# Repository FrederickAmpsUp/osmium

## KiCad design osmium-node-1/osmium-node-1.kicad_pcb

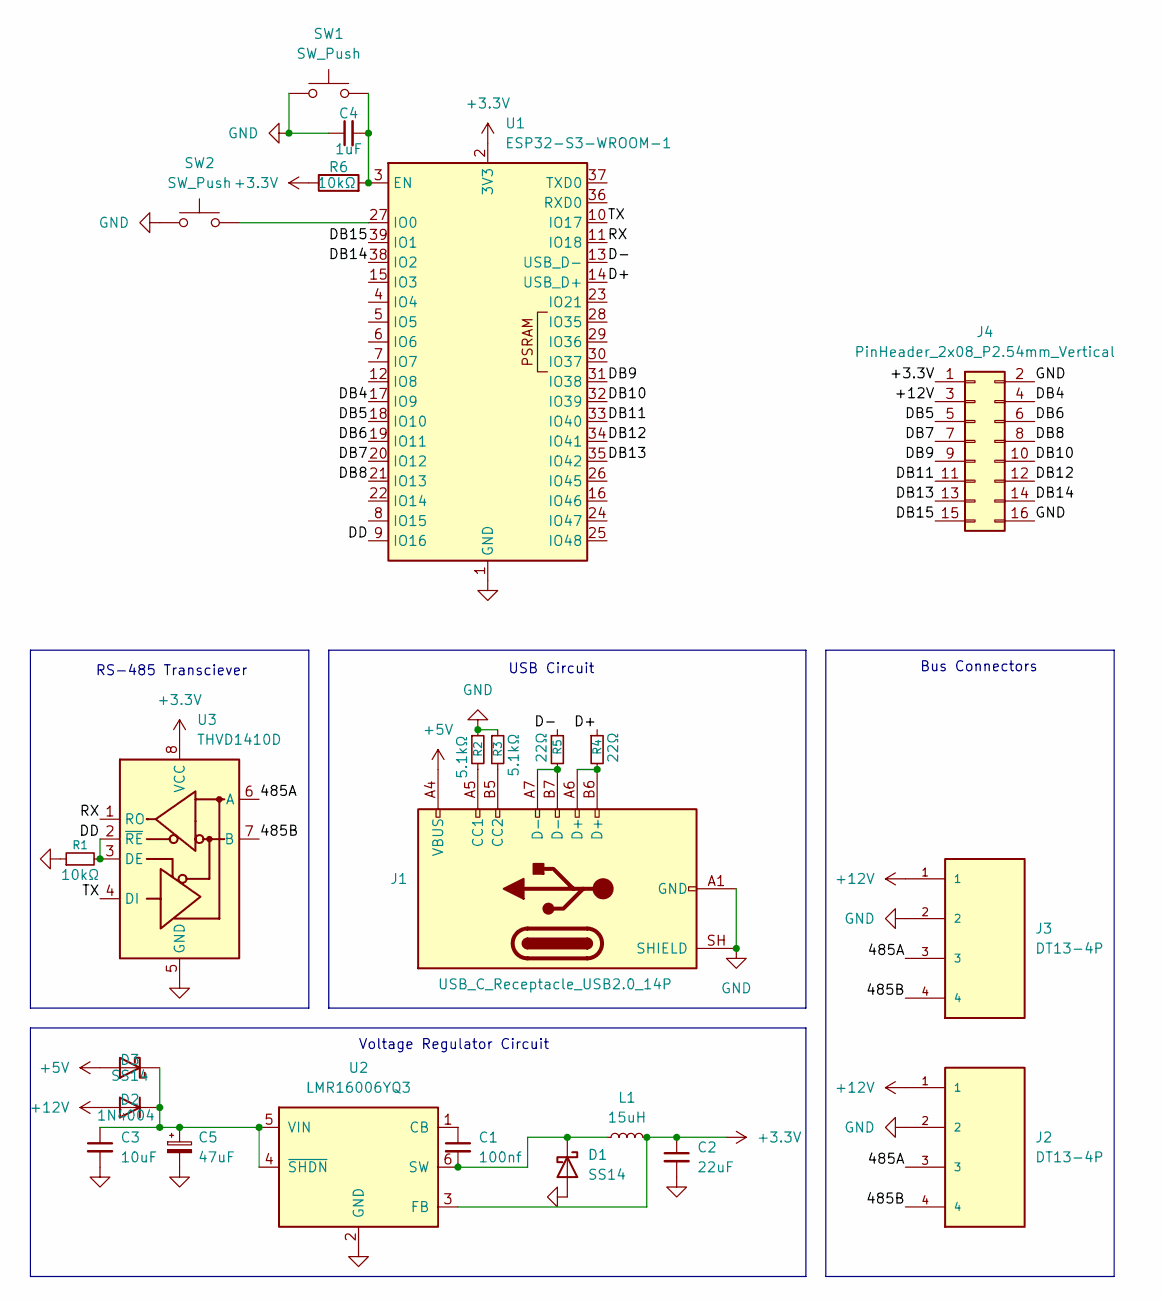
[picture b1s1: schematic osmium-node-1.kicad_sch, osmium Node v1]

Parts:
C1: 100nf; C_0805_2012Metric
C2: 22uF; C_1206_3216Metric
C3: 10uF; C_1206_3216Metric
C4: 1uF; C_0805_2012Metric
C5: 47uF; CP_Elec_6.3x5.4
D1, D3: SS14; D_SMA
D2: 1N4004; D_DO-41_SOD81_P10.16mm_Horizontal
J1: USB_C_Receptacle_USB2.0_14P; GCT_USB4120-03-C_REVA6
J2, J3: DT13-4P; TE_DT13-4P; PARTREV C1
J4: PinHeader_2x08_P2.54mm_Vertical
L1: 15uH; L_7.3x7.3_H4.5
R1, R6: 10kΩ; R_0805_2012Metric
R2, R3: 5.1kΩ; R_0805_2012Metric
R4, R5: 22Ω; R_0805_2012Metric
SW1, SW2: SW_Push; SW_PUSH_6mm
U1: ESP32-S3-WROOM-1
U2: LMR16006YQ3; SOT-23-6
U3: THVD1410D; SOIC-8_3.9x4.9mm_P1.27mm

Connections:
+3.3V: C2.1, J4.1, L1.2, R6.1, U1.2 (3V3), U2.3 (FB), U3.8 (VCC)
+5V: D3.2 (A), J1.A4 (VBUS), J1.A9 (VBUS), J1.B4 (VBUS), J1.B9 (VBUS)
+12V: D2.2 (A), J2.1, J3.1, J4.3
/485A: J2.3, J3.3, U3.6 (A)
/485B: J2.4, J3.4, U3.7 (B)
/D+: R4.1, U1.14 (USB_D+)
/D-: R5.1, U1.13 (USB_D-)
/DB4: J4.4, U1.17 (IO9)
/DB5: J4.5, U1.18 (IO10)
/DB6: J4.6, U1.19 (IO11)
/DB7: J4.7, U1.20 (IO12)
/DB8: J4.8, U1.21 (IO13)
/DB9: J4.9, U1.31 (IO38)
/DB10: J4.10, U1.32 (IO39)
/DB11: J4.11, U1.33 (IO40)
/DB12: J4.12, U1.34 (IO41)
/DB13: J4.13, U1.35 (IO42)
/DB14: J4.14, U1.38 (IO2)
/DB15: J4.15, U1.39 (IO1)
/DD: R1.2, U1.9 (IO16), U3.2 (~RE), U3.3 (DE)
/RX: U1.11 (IO18), U3.1 (RO)
/TX: U1.10 (IO17), U3.4 (DI)
GND: C2.2, C3.2, C4.1, C5.2, D1.2 (A), J1.A1 (GND), J1.A12 (GND), J1.B1 (GND), J1.B12 (GND), J1.S1, J1.S2, J1.S3, J1.S4, J1.SH (SHIELD), J2.2, J3.2, J4.2, J4.16, R1.1, R2.1, R3.1, SW1.1, SW2.1, U1.1 (GND), U1.40 (GND), U1.41 (GND), U2.2 (GND), U3.5 (GND)
unnamed: C1.2, D1.1 (K), L1.1, U2.6 (SW)
unnamed: C3.1, C5.1, D2.1 (K), D3.1 (K), U2.4 (~SHDN), U2.5 (VIN)
unnamed: J1.A5 (CC1), R2.2
unnamed: J1.B5 (CC2), R3.2
unnamed: J1.A6 (D+), J1.B6 (D+), R4.2
unnamed: J1.A7 (D-), J1.B7 (D-), R5.2
unnamed: C4.2, R6.2, SW1.2, U1.3 (EN)
unnamed: SW2.2, U1.27 (IO0)
unnamed: C1.1, U2.1 (CB)

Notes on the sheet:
Bus Connectors
RS-485 Transciever
USB Circuit
Voltage Regulator Circuit

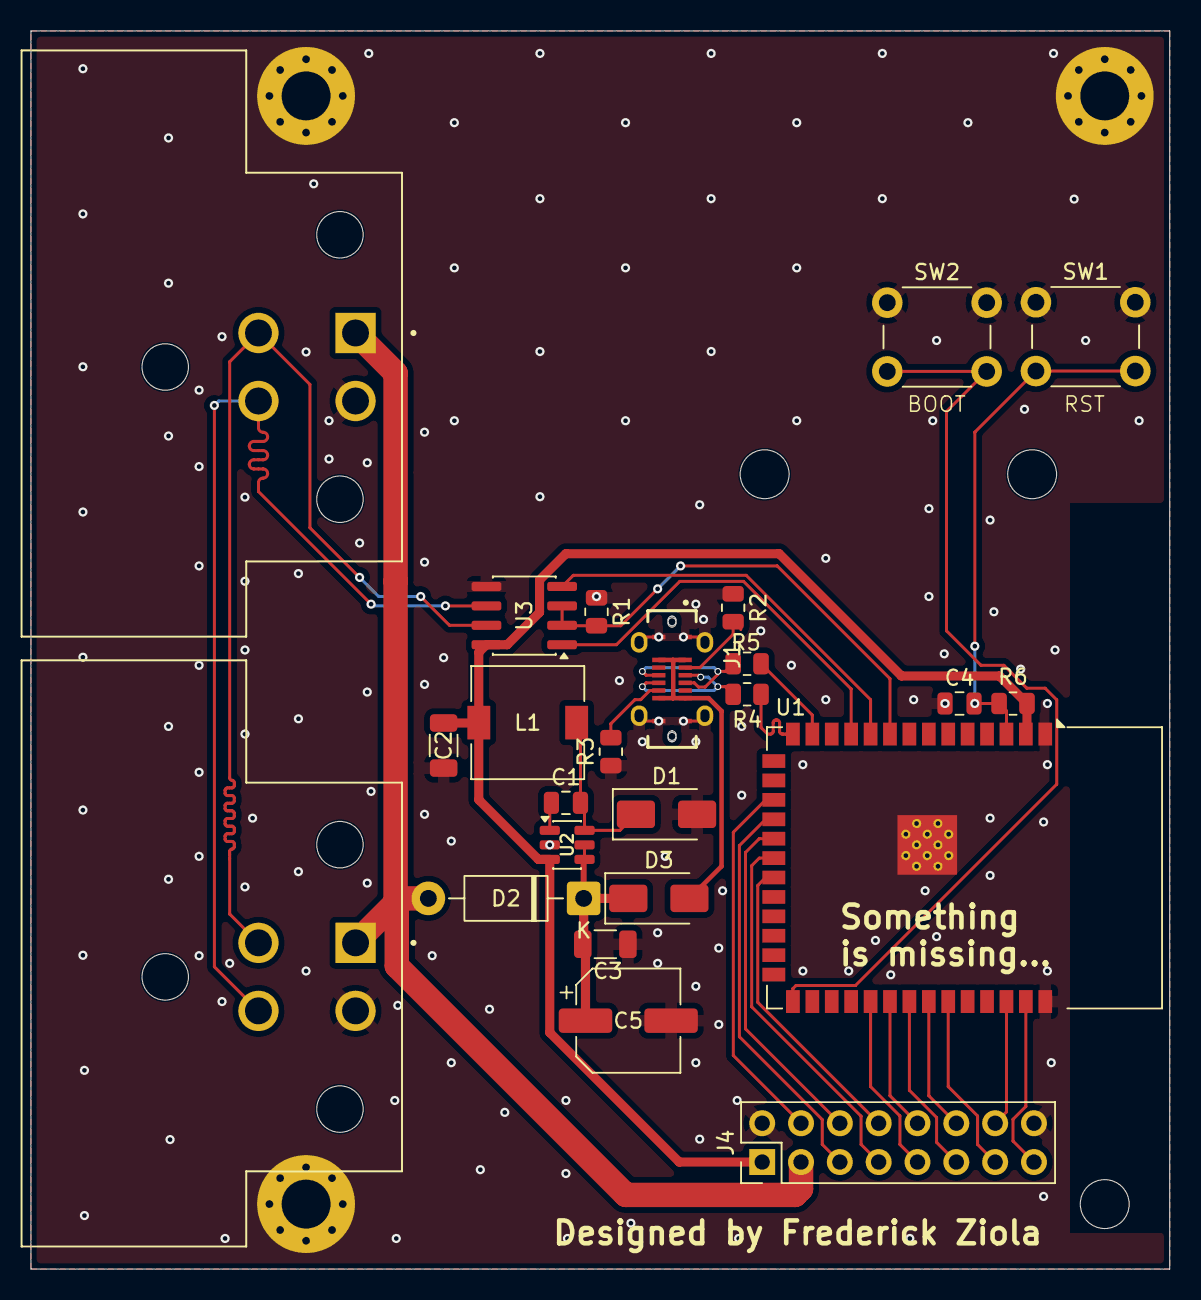
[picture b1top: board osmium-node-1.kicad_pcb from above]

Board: 2 copper layers, 74.5 x 81.0 mm, 24 parts (0 on the bottom side), 32 nets.

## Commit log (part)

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2026-06-23 small documentation
2026-06-23 refactor to remove circular include
2026-06-24 logging system working, running on devboard
2026-06-24 Add gitignore in PCB folder
2026-06-24 remove gitfile
2026-06-24 refactor serialsink
2026-06-24 make rs485 stream-compatible
2026-06-24 start implementing nodebus parser
2026-06-25 Nodebus parser v1 done
2026-06-26 Update nodebus protocol and refactor
2026-06-26 Implement nodebus sender
2026-06-26 refactoring
2026-06-26 minor change
